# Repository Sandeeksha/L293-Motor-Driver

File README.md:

# Motor Driver Circuit using L293D and 5V Regulator

This project contains the schematic and PCB for a **motor driver circuit** using an **L293D H-Bridge IC**, with a regulated 5V supply provided by a **7805 voltage regulator**.

Schematic Diagram: 

PCB Diagram: 

3D View of Front Side PCB: 

3D View of Back Side PCB:

## ⚙️ Circuit Description

- **Input Power:**
  - External voltage is supplied via connector `J2`.
  - The **7805 voltage regulator** (`U2`) regulates the voltage down to **5V** for logic operation and powering low-power peripherals.
- **Motor Driver (L293D):**
  - The `L293D` (`U1`) is a dual H-bridge motor driver IC used to drive two DC motors independently.
  - Control inputs for the motor driver are provided through connector `J1` (4-pin header).
- **Outputs:**
  - Motor outputs are available at connectors `J3` and `J4`, each controlling one motor.
- **Status Indication:**
  - An LED (`D1`) with a current-limiting resistor (`R1`) is used to indicate that the 5V regulated power is available.
- **Power Flags:**
  - `PWR_FLAG` symbols are added for validation to indicate power availability in schematic design tools.

## 🧩Components

| Reference | Component    | Description                     |
|:---------:|:-------------:|:-------------------------------:|
| U1        | L293D         | Dual H-Bridge Motor Driver IC    |
| U2        | 7805          | 5V Linear Voltage Regulator IC   |
| J1        | Header        | Motor Control Input Connector    |
| J2        | Screw Terminal| External Voltage Input Connector |
| J3, J4    | Screw Terminals| Motor Output Connectors         |
| R1        | Resistor      | LED Current Limiting Resistor    |
| D1        | LED           | Power Status Indicator          |

## 🚀 How It Works

1. External power is connected to the circuit through `J2`.
2. `U2` (7805) steps down the input voltage to 5V DC to power the logic circuitry.
3. Control signals (e.g., PWM, direction control) are provided to `J1`.
4. `U1` (L293D) uses these signals to drive two motors connected via `J3` and `J4`.
5. The LED (`D1`) lights up to indicate that 5V regulated power is available and the system is active.

 ## 🚀 How to Use

- Connect a DC input voltage to **J2**.
- Connect control signals (motor directions) to **J1**.
- Connect your DC motors to **J3** and **J4**.
- Power up and control your motors!

## 🛠️ License

This project is open-source and free to use.

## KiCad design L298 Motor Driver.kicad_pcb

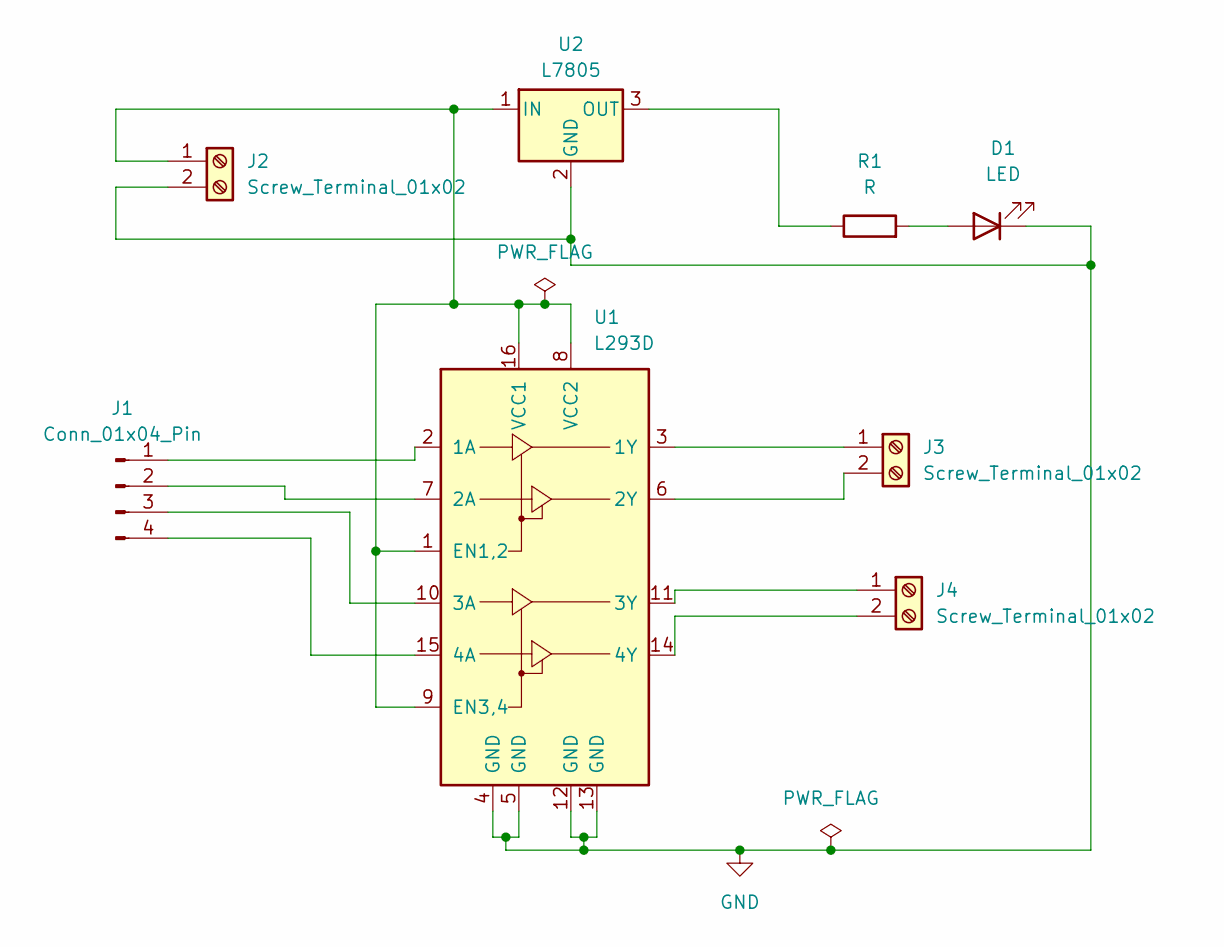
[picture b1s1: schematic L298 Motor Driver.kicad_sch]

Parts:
D1: LED; LED_D3.0mm
J1: Conn_01x04_Pin; FanPinHeader_1x04_P2.54mm_Vertical
J2, J3, J4: Screw_Terminal_01x02; TerminalBlock_Phoenix_MKDS-1,5-2-5.08_1x02_P5.08mm_Horizont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
R1: R; R_Axial_DIN0204_L3.6mm_D1.6mm_P5.08mm_Horizontal
U1: L293D; DIP-16_W7.62mm
U2: L7805; TO-220-3_Vertical

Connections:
GND: D1.1 (K), J2.2, U1.4 (GND), U1.5 (GND), U1.12 (GND), U1.13 (GND), U2.2 (GND)
unnamed: D1.2 (A), R1.2
unnamed: J1.1, U1.2 (1A)
unnamed: J1.2, U1.7 (2A)
unnamed: J1.3, U1.10 (3A)
unnamed: J1.4, U1.15 (4A)
unnamed: J2.1, U1.1 (EN1,2), U1.8 (VCC2), U1.9 (EN3,4), U1.16 (VCC1), U2.1 (IN)
unnamed: J3.1, U1.3 (1Y)
unnamed: J3.2, U1.6 (2Y)
unnamed: J4.1, U1.11 (3Y)
unnamed: J4.2, U1.14 (4Y)
unnamed: R1.1, U2.3 (OUT)

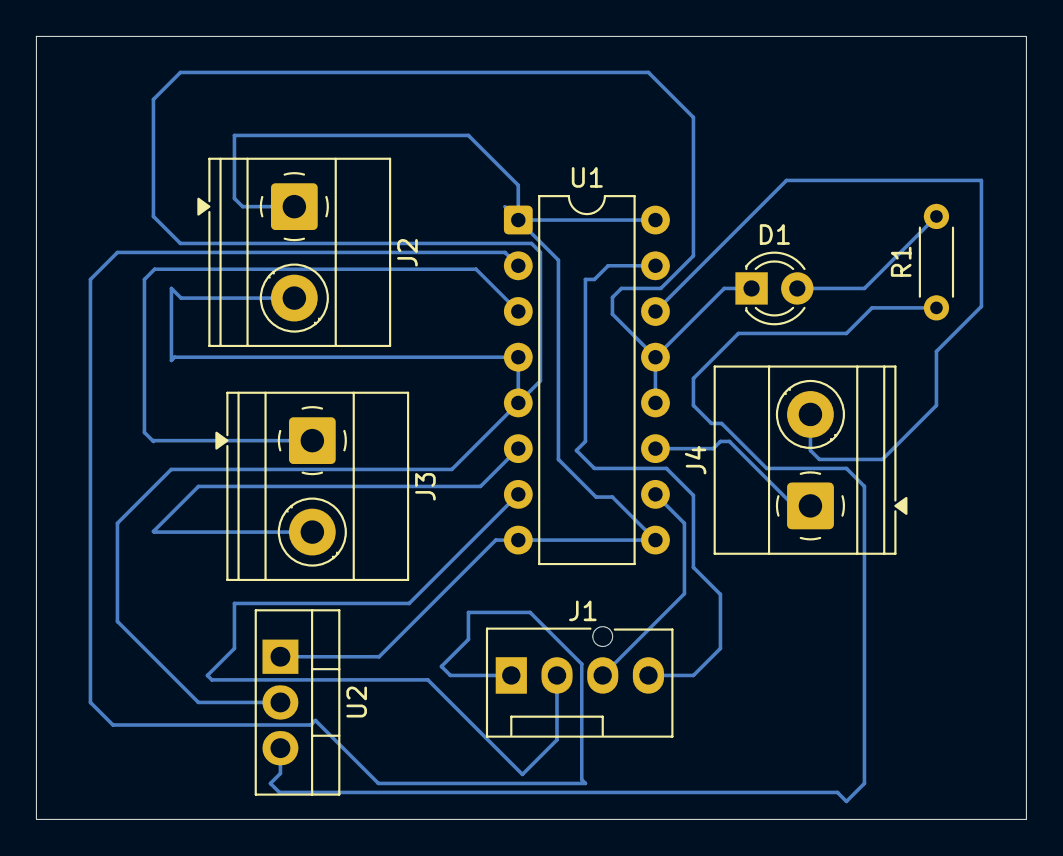
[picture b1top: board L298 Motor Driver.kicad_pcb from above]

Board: 2 copper layers, 55.0 x 43.5 mm, 8 parts (0 on the bottom side), 12 nets.

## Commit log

2025-04-28 Initial Stage
2025-04-28 L293D Driver Circuit
2025-04-28 this is final version
2025-04-28 done
